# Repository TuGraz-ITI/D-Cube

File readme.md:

# D-Cube Benchmark #
The entire software stack for the ([public D-Cube instance](https://iti-testbed.tugraz.at/overview)) has been released as open-source as well and can be found ([here](https://github.com/TuGraz-ITI/D-Cube-Benchmark)). The initial documentation of the stack is avaialble ([here](https://tugraz-iti.github.io)).

# D-Cube Design #

D-Cube is published as open source hardware under [CC-BY-SA](license.md) ([online](https://creativecommons.org/licenses/by-sa/4.0/deed.en)).
D-Cube is a low-cost tool that allows to accurately profile the end-to-end delay, reliability, and power consumption, of low-power wireless sensor nodes, as well as to graphically visualize their evolution in real-time.
This tool has been used to set-up the EWSN 2016, 2017 and 2018 dependability competitions.
* [EWSN 2016 Dependability Competition (Graz, Austria)](http://ewsn2016.tugraz.at/cms/index.php?id=49)  
* [EWSN 2017 Dependability Competition (Uppsala, Sweden)](http://www.ewsn2017.org/dependability-competition1.html)
* [EWSN 2018 Dependability Competition (Madrid, Spain)](https://ewsn2018.networks.imdea.org/competition-program.html)
* [EWSN 2019 Dependability Competition (Beijing, China)](http://ewsn2019.thss.tsinghua.edu.cn/competition-scenario.html)

A scientific paper about D-Cube was published at the 14th International Conference on Embedded Wireless Systems and Networks (EWSN), and is available [here](http://www.carloalbertoboano.com/documents/boano17competition.pdf). 
An scientific paper describing D-Cube's binary patching capability and explaining how to use D-Cube to benchmark low-power wireless systems was published at the 1st International Workshop on Benchmarking Cyber-Physical Networks and Systems (CPSBench), and can be downloaded [here](http://www.carloalbertoboano.com/documents/schuss18benchmark.pdf).  
A set of slides giving a brief overview of D-Cube's capabilities and architecture can be found [here](http://www.carloalbertoboano.com/documents/D-Cube_overview.pdf).  

## D-Cube Hardware ##
The design files in this repository where used to fabricate the current iteration of D-Cube. The GPS module used is a Navspark-GL. For the complementary MOSFET a NTJD4105CT2G was chosen in the final design.

### The current version of the hardware (2.1) ###
The current version of the hardware supports multiple bi-directional GPIOs via isolation. It also adds support for PoE via a PEM1305 module. The aging navspark has been replaced with a more generic ublox neo footprint.

### The orignal version of the hardware (1.0) ###

### The prototype used during EWSN 2016 ###

## D-Cube Software ##
The Software consists of two parts
* A task reading the ADC into a FIFO (on top of a real-time Linux kernel)
* A task reading the FIFO and writing it to the database (InfluxDB)

D-Cube contains a power switch circuit which controls the power before the DCDC isolator. A high signal on GPIO23 is required for the ADC and the target to be supplied with power. The gpio.sh file contains an example for this.

### Real-Time Linux ###
We used https://github.com/emlid/linux-rt-rpi but others should work fine

### Visualisation ###
InfluxDB has many frontends available, we used grafana (http://grafana.org/)

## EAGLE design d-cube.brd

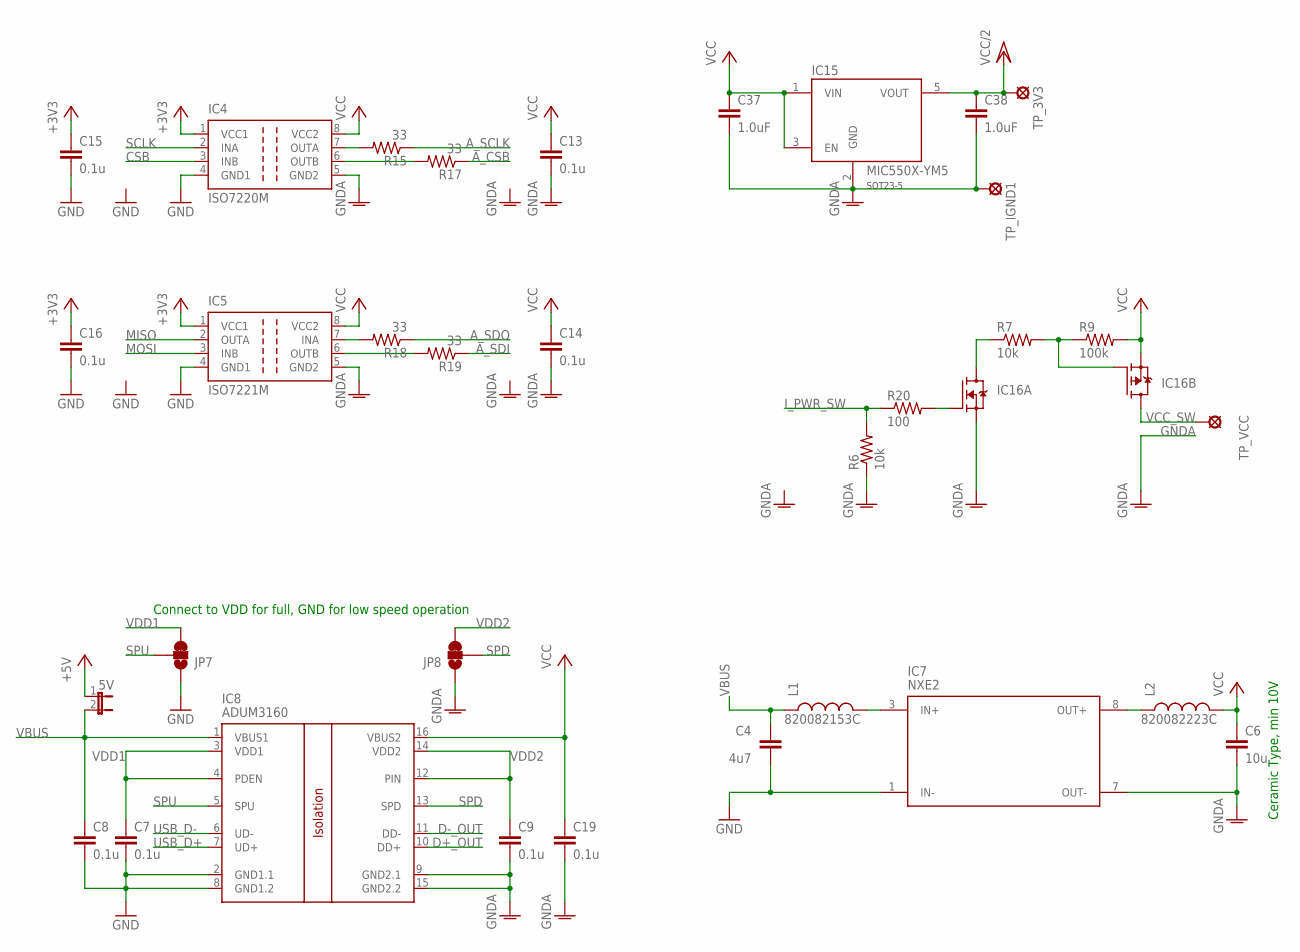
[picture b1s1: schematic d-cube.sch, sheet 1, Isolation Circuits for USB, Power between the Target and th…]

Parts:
5V: JP1E; JP1
C4: 4u7; 0805
C6: 10u; 0805
C7, C8, C9, C13, C14, C15, C16, C19: 0.1u; 0402-CAP
C37, C38: 1.0uF; 0805
IC4: ISO7220M; SO-08
IC5: ISO7221M; SO-08
IC7: NXE2
IC8: ADUM3160; SO-16W
IC15: MIC550X-YM5; SOT23-5-DBV
IC16: COMPLEMENTARY; SOT-363
JP7, JP8: JUMPER-PAD-3-2OF3_NC_BY_TRACE_LARGE; PAD-JUMPER-3-2OF3_NC_BY_TRACE_YES_SILK_LARGE
L1: 820082153C; 8200
L2: 820082223C; 8200
R6, R7: 10k; 0402-RES
R9: 100k; 0402-RES
R15, R17, R18, R19: 33; 0402-RES
R20: 100; 0402-RES
TP_3V3: LSP10
TP_IGND1: LSP10
TP_VCC: LSP10

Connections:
+3V3: C15.1, C16.1, IC4.1 (VCC1), IC5.1 (VCC1); also elsewhere on the board
+5V: 5V.1; also elsewhere on the board
A_CSB: R17.1; also elsewhere on the board
A_SCLK: R15.1; also elsewhere on the board
A_SDI: R19.1; also elsewhere on the board
A_SDO: R18.1; also elsewhere on the board
CSB: IC4.3 (INB); also elsewhere on the board
D+_OUT: IC8.10 (DD+); also elsewhere on the board
D-_OUT: IC8.11 (DD-); also elsewhere on the board
GND: C4.2, C7.2, C8.2, C15.2, C16.2, IC4.4 (GND1), IC5.4 (GND1), IC7.1 (IN-), IC8.2 (GND1.1), IC8.8 (GND1.2), JP7.1; also elsewhere on the board
GNDA: C6.2, C9.2, C13.2, C14.2, C19.2, C37.2, C38.2, IC4.5 (GND2), IC5.5 (GND2), IC7.7 (OUT-), IC8.9 (GND2.1), IC8.15 (GND2.2), IC15.2 (GND), IC16.1 (S), JP8.1, R6.1, TP_IGND1.MP; also elsewhere on the board
I_PWR_SW: R6.2, R20.1; also elsewhere on the board
MISO: IC5.2 (OUTA); also elsewhere on the board
MOSI: IC5.3 (INB); also elsewhere on the board
unnamed: IC7.3 (IN+), L1.P$2 (2)
unnamed: IC16.2 (G), R20.2
unnamed: IC16.5 (G), R7.2, R9.1
unnamed: IC7.8 (OUT+), L2.P$1 (1)
unnamed: IC16.6 (D), R7.1
unnamed: IC4.7 (OUTA), R15.2
unnamed: IC4.6 (OUTB), R17.2
unnamed: IC5.7 (INA), R18.2
unnamed: IC5.6 (OUTB), R19.2
SCLK: IC4.2 (INA); also elsewhere on the board
SPD: IC8.13 (SPD), JP8.2
SPU: IC8.5 (SPU), JP7.2
USB_D+: IC8.7 (UD+); also elsewhere on the board
USB_D-: IC8.6 (UD-); also elsewhere on the board
VBUS: 5V.2, C4.1, C8.1, IC8.1 (VBUS1), L1.P$1 (1); also elsewhere on the board
VCC: C6.1, C13.1, C14.1, C19.1, C37.1, IC4.8 (VCC2), IC5.8 (VCC2), IC8.16 (VBUS2), IC15.1 (VIN), IC15.3 (EN), IC16.4 (S), L2.P$2 (2), R9.2; also elsewhere on the board
VCC/2: C38.1, IC15.5 (VOUT), TP_3V3.MP; also elsewhere on the board
VCC_SW: IC16.3 (D), TP_VCC.MP; also elsewhere on the board
VDD1: C7.1, IC8.3 (VDD1), IC8.4 (PDEN), JP7.3
VDD2: C9.1, IC8.12 (PIN), IC8.14 (VDD2), JP8.3

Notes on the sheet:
Connect to VDD for full, GND for low speed operation
Ceramic Type, min 10V

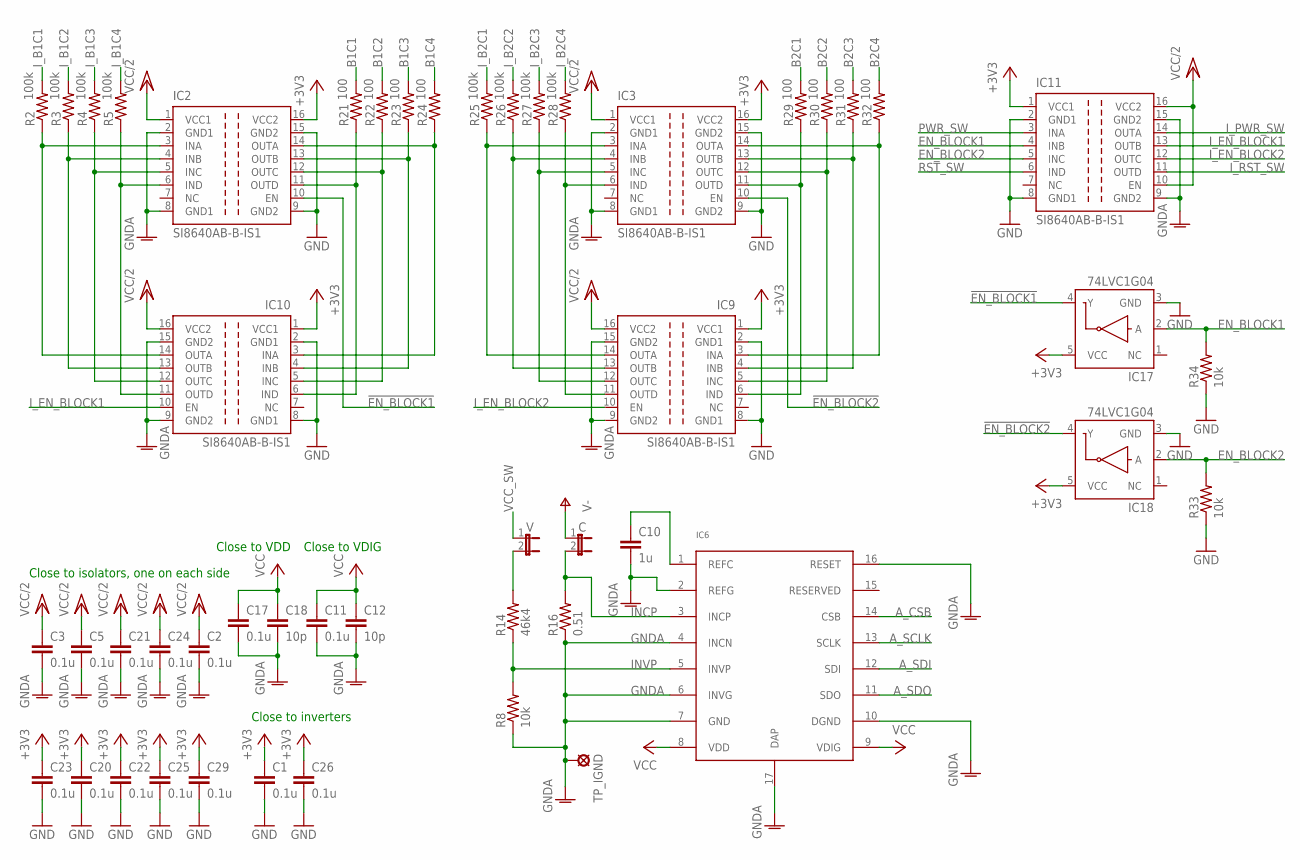
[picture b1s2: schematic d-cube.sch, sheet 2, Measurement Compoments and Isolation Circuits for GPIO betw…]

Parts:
C: JP1E; JP1
C1, C2, C3, C5, C11, C17, C20, C21, C22, C23, C24, C25, C26, C29: 0.1u; 0402-CAP
C10: 1u; 0402-CAP
C12, C18: 10p; 0402-CAP
IC2, IC3, IC9, IC10, IC11: SI8640AB-B-IS1; SO-16
IC6: LMP92064; WSON-16
IC17, IC18: 74LVC1G04; SOT353
R2, R3, R4, R5, R25, R26, R27, R28: 100k; 0402-RES
R8: 10k; 0805
R14: 46k4; 0805
R16: 0.51; 1206
R21, R22, R23, R24, R29, R30, R31, R32: 100; 0402-RES
R33, R34: 10k; 0402-RES
TP_IGND: LSP10
V: JP1E; JP1

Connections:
!EN_BLOCK1: IC2.10 (EN), IC17.4 (Y)
!EN_BLOCK2: IC3.10 (EN), IC18.4 (Y)
+3V3: C1.1, C20.1, C22.1, C23.1, C25.1, C26.1, C29.1, IC2.16 (VCC2), IC3.16 (VCC2), IC9.1 (VCC1), IC10.1 (VCC1), IC11.1 (VCC1), IC17.5 (VCC), IC18.5 (VCC); also elsewhere on the board
A_CSB: IC6.14 (CSB); also elsewhere on the board
A_SCLK: IC6.13 (SCLK); also elsewhere on the board
A_SDI: IC6.12 (SDI); also elsewhere on the board
A_SDO: IC6.11 (SDO); also elsewhere on the board
B1C1: R21.2; also elsewhere on the board
B1C2: R22.2; also elsewhere on the board
B1C3: R23.2; also elsewhere on the board
B1C4: R24.2; also elsewhere on the board
B2C1: R29.2; also elsewhere on the board
B2C2: R30.2; also elsewhere on the board
B2C3: R31.2; also elsewhere on the board
B2C4: R32.2; also elsewhere on the board
EN_BLOCK1: IC11.4 (INB), IC17.2 (A), R34.2; also elsewhere on the board
EN_BLOCK2: IC11.5 (INC), IC18.2 (A), R33.2; also elsewhere on the board
GND: C1.2, C20.2, C22.2, C23.2, C25.2, C26.2, C29.2, IC2.9 (GND2), IC2.15 (GND2), IC3.9 (GND2), IC3.15 (GND2), IC9.2 (GND1), IC9.8 (GND1), IC10.2 (GND1), IC10.8 (GND1), IC11.2 (GND1), IC11.8 (GND1), IC17.3 (GND), IC18.3 (GND), R33.1, R34.1; also elsewhere on the board
GNDA: C2.2, C3.2, C5.2, C10.2, C11.2, C12.2, C17.2, C18.2, C21.2, C24.2, IC2.2 (GND1), IC2.8 (GND1), IC3.2 (GND1), IC3.8 (GND1), IC6.2 (REFG), IC6.4 (INCN), IC6.6 (INVG), IC6.7 (GND), IC6.10 (DGND), IC6.16 (RESET), IC6.17 (DAP), IC9.9 (GND2), IC9.15 (GND2), IC10.9 (GND2), IC10.15 (GND2), IC11.9 (GND2), IC11.15 (GND2), R8.1, R16.1, TP_IGND.MP; also elsewhere on the board
INCP: C.2, IC6.3 (INCP), R16.2
INVP: IC6.5 (INVP), R8.2, R14.1
I_B1C1: R2.2; also elsewhere on the board
I_B1C2: R3.2; also elsewhere on the board
I_B1C3: R4.2; also elsewhere on the board
I_B1C4: R5.2; also elsewhere on the board
I_B2C1: R25.2; also elsewhere on the board
I_B2C2: R26.2; also elsewhere on the board
I_B2C3: R27.2; also elsewhere on the board
I_B2C4: R28.2; also elsewhere on the board
I_EN_BLOCK1: IC10.10 (EN), IC11.13 (OUTB)
I_EN_BLOCK2: IC9.10 (EN), IC11.12 (OUTC)
I_PWR_SW: IC11.14 (OUTA); also elsewhere on the board
I_RST_SW: IC11.11 (OUTD); also elsewhere on the board
unnamed: IC2.3 (INA), IC10.14 (OUTA), R2.1
unnamed: IC2.14 (OUTA), IC10.3 (INA), R24.1
unnamed: IC2.13 (OUTB), IC10.4 (INB), R23.1
unnamed: IC2.12 (OUTC), IC10.5 (INC), R22.1
unnamed: IC3.3 (INA), IC9.14 (OUTA), R25.1
unnamed: IC2.6 (IND), IC10.11 (OUTD), R5.1
unnamed: IC2.5 (INC), IC10.12 (OUTC), R4.1
unnamed: IC2.4 (INB), IC10.13 (OUTB), R3.1
unnamed: C10.1, IC6.1 (REFC)
unnamed: IC2.11 (OUTD), IC10.6 (IND), R21.1
unnamed: R14.2, V.2
unnamed: IC3.6 (IND), IC9.11 (OUTD), R28.1
unnamed: IC3.5 (INC), IC9.12 (OUTC), R27.1
unnamed: IC3.4 (INB), IC9.13 (OUTB), R26.1
unnamed: IC3.14 (OUTA), IC9.3 (INA), R32.1
unnamed: IC3.13 (OUTB), IC9.4 (INB), R31.1
unnamed: IC3.12 (OUTC), IC9.5 (INC), R30.1
unnamed: IC3.11 (OUTD), IC9.6 (IND), R29.1
PWR_SW: IC11.3 (INA); also elsewhere on the board
RST_SW: IC11.6 (IND); also elsewhere on the board
V-: C.1; also elsewhere on the board
VCC: C11.1, C12.1, C17.1, C18.1, IC6.8 (VDD), IC6.9 (VDIG); also elsewhere on the board
VCC/2: C2.1, C3.1, C5.1, C21.1, C24.1, IC2.1 (VCC1), IC3.1 (VCC1), IC9.16 (VCC2), IC10.16 (VCC2), IC11.10 (EN), IC11.16 (VCC2); also elsewhere on the board
VCC_SW: V.1; also elsewhere on the board

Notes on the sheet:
Close to inverters
Close to isolators, one on each side
Close to VDD
Close to VDIG

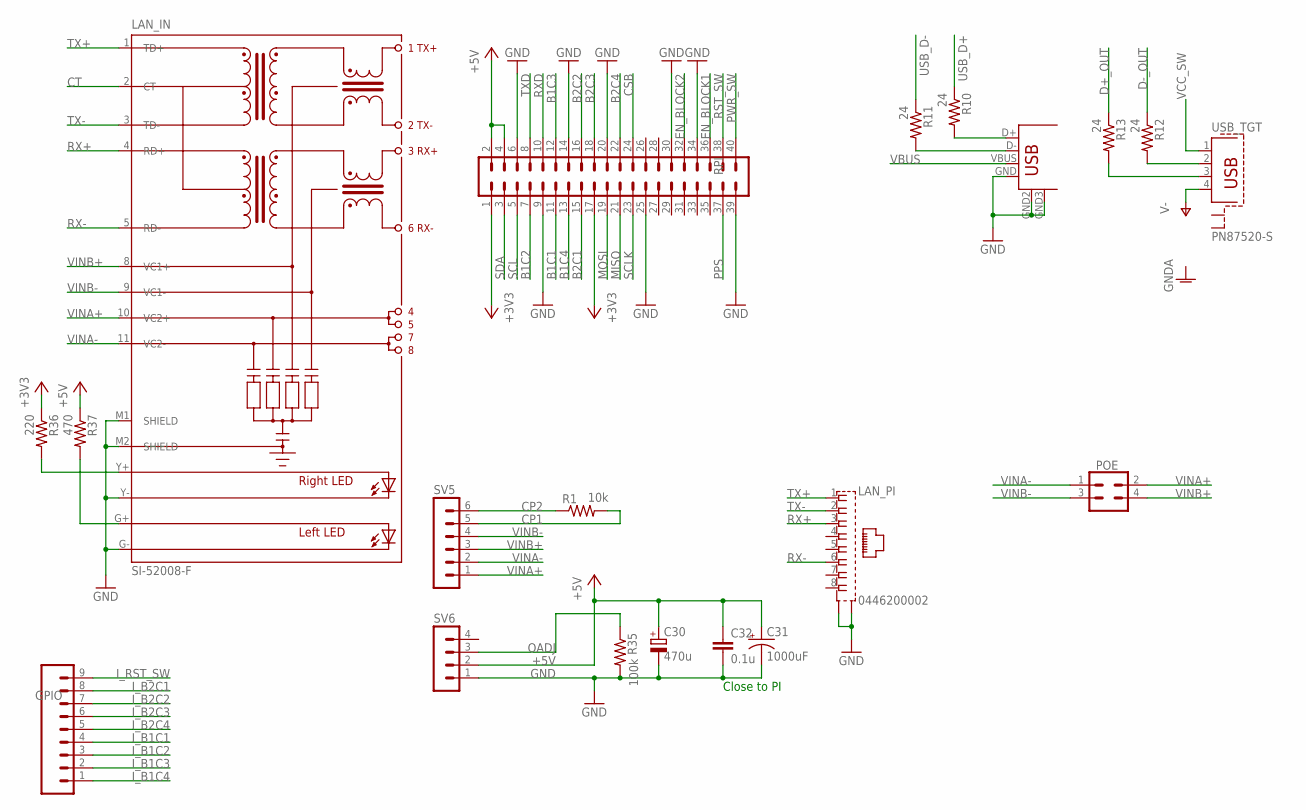
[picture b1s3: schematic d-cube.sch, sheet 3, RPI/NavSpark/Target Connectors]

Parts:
C30: 470u; CT7343
C31: 1000uF; PANASONIC_G
C32: 0.1u; 0805
GPIO: CONN_09NO_SILK; 1X09_NO_SILK
LAN_IN: SI-52008-F; POE
LAN_PI: 0446200002
POE: CONN_02X2; 2X02_NO_SILK
R1: 10k; 0402-RES
R10, R11, R12, R13: 24; 0402-RES
R35: 100k; 0402-RES
R36: 220; 0402-RES
R37: 470; 0402-RES
RPI: MA20-2
SV5: MA06-1
SV6: MA04-1
USB_PI: USB+SHIELDUSB-A-H-S; USB-A-H
USB_TGT: PN87520-S

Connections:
+3V3: R36.1, RPI.1, RPI.17; also elsewhere on the board
+5V: C30.+, C31.+, C32.1, R37.1, RPI.2, RPI.4, SV6.2; also elsewhere on the board
B1C1: RPI.11; also elsewhere on the board
B1C2: RPI.7; also elsewhere on the board
B1C3: RPI.12; also elsewhere on the board
B1C4: RPI.13; also elsewhere on the board
B2C1: RPI.15; also elsewhere on the board
B2C2: RPI.16; also elsewhere on the board
B2C3: RPI.18; also elsewhere on the board
B2C4: RPI.22; also elsewhere on the board
CP1: R1.2, SV5.5
CP2: R1.1, SV5.6
CSB: RPI.24; also elsewhere on the board
CT: LAN_IN.2 (CT)
D+_OUT: R13.1; also elsewhere on the board
D+_OUT_TERM: R13.2, USB_TGT.3
D-_OUT: R12.1; also elsewhere on the board
D-_OUT_TERM: R12.2, USB_TGT.2
EN_BLOCK1: RPI.36; also elsewhere on the board
EN_BLOCK2: RPI.32; also elsewhere on the board
GND: C30.-, C31.-, C32.2, LAN_IN.G- (C-L), LAN_IN.M1 (SHIELD), LAN_IN.M2 (SHIELD), LAN_IN.Y- (C-R), LAN_PI.S@1 (S1), LAN_PI.S@2 (S2), R35.2, RPI.6, RPI.9, RPI.14, RPI.20, RPI.25, RPI.30, RPI.34, RPI.39, SV6.1, USB_PI.GND, USB_PI.GND2 (S1), USB_PI.GND3 (S2); also elsewhere on the board
I_B1C1: GPIO.4; also elsewhere on the board
I_B1C2: GPIO.3; also elsewhere on the board
I_B1C3: GPIO.2; also elsewhere on the board
I_B1C4: GPIO.1; also elsewhere on the board
I_B2C1: GPIO.8; also elsewhere on the board
I_B2C2: GPIO.7; also elsewhere on the board
I_B2C3: GPIO.6; also elsewhere on the board
I_B2C4: GPIO.5; also elsewhere on the board
I_RST_SW: GPIO.9; also elsewhere on the board
MISO: RPI.21; also elsewhere on the board
MOSI: RPI.19; also elsewhere on the board
unnamed: LAN_IN.Y+ (A-R), R36.2
unnamed: LAN_IN.G+ (A-L), R37.2
OADJ: R35.1, SV6.3
PPS: RPI.37; also elsewhere on the board
PWR_SW: RPI.40; also elsewhere on the board
RST_SW: RPI.38; also elsewhere on the board
RX+: LAN_IN.4 (RD+), LAN_PI.3
RX-: LAN_IN.5 (RD-), LAN_PI.6
RXD: RPI.10; also elsewhere on the board
SCL: RPI.5; also elsewhere on the board
SCLK: RPI.23; also elsewhere on the board
SDA: RPI.3; also elsewhere on the board
TX+: LAN_IN.1 (TD+), LAN_PI.1
TX-: LAN_IN.3 (TD-), LAN_PI.2
TXD: RPI.8; also elsewhere on the board
USB_D+: R10.1; also elsewhere on the board
USB_D+_TERM: R10.2, USB_PI.D+
USB_D-: R11.1; also elsewhere on the board
USB_D-_TERM: R11.2, USB_PI.D-
V-: USB_TGT.4; also elsewhere on the board
VBUS: USB_PI.VBUS; also elsewhere on the board
VCC_SW: USB_TGT.1; also elsewhere on the board
VINA+: LAN_IN.10 (VC2+), POE.2, SV5.1
VINA-: LAN_IN.11 (VC2-), POE.1, SV5.2
VINB+: LAN_IN.8 (VC1+), POE.4, SV5.3
VINB-: LAN_IN.9 (VC1-), POE.3, SV5.4

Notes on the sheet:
Close to PI

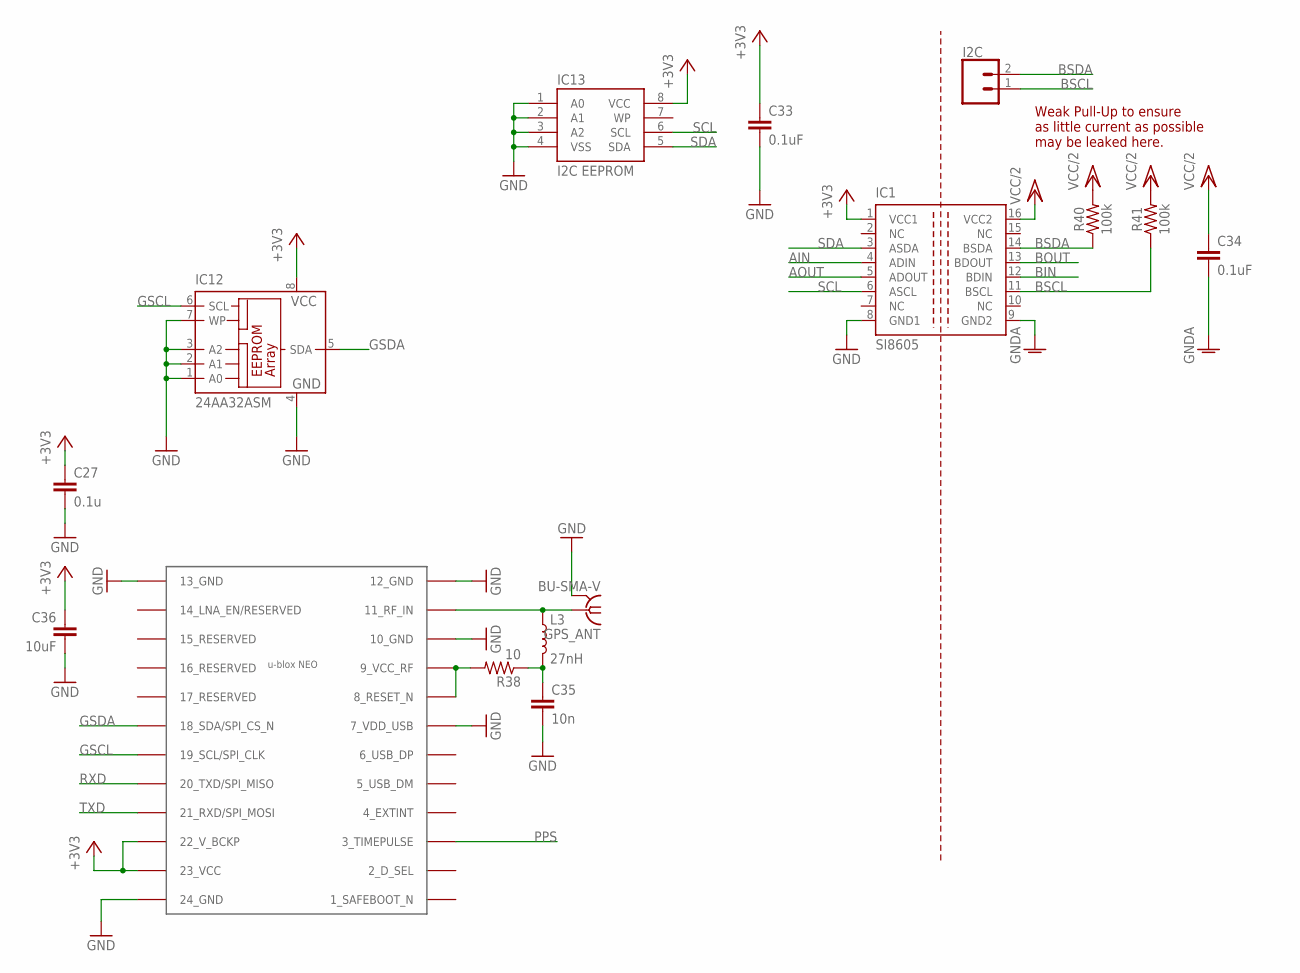
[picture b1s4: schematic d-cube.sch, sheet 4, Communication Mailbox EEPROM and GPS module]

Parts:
C27: 0.1u; 0402-CAP
C33, C34: 0.1uF; 0402
C35: 10n; 0805
C36: 10uF; 0805
GPS_ANT: BU-SMA-V
I2C: CONN_021X02_NO_SILK; 1X02_NO_SILK
IC1: SI8605; SO-16
IC12: 24AA32ASM; SO-08M
IC13: I2C EEPROM; SO08-EIAJ
IC14: NEO-M8
L3: 27nH; 0402
R38: 10; 0402-RES
R40, R41: 100k; 0402

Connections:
+3V3: C27.1, C33.1, C36.1, IC1.1 (VCC1), IC12.8 (VCC), IC13.8 (VCC), IC14.22 (22_V_BCKP), IC14.23 (23_VCC); also elsewhere on the board
AIN: IC1.4 (ADIN)
AOUT: IC1.5 (ADOUT)
BIN: IC1.12 (BDIN)
BOUT: IC1.13 (BDOUT)
BSCL: I2C.1, IC1.11 (BSCL), R41.1
BSDA: I2C.2, IC1.14 (BSDA), R40.1
GND: C27.2, C33.2, C35.2, C36.2, GPS_ANT.2 (GND), GPS_ANT.3 (GND), GPS_ANT.4 (GND), GPS_ANT.5 (GND), IC1.8 (GND1), IC12.1 (A0), IC12.2 (A1), IC12.3 (A2), IC12.4 (GND), IC12.7 (WP), IC13.1 (A0), IC13.2 (A1), IC13.3 (A2), IC13.4 (VSS), IC14.7 (7_VDD_USB), IC14.10 (10_GND), IC14.12 (12_GND), IC14.13 (13_GND), IC14.24 (24_GND); also elsewhere on the board
GNDA: C34.2, IC1.9 (GND2); also elsewhere on the board
GPS_SIG: GPS_ANT.1, IC14.11 (11_RF_IN), L3.1
GSCL: IC12.6 (SCL), IC14.19 (19_SCL/SPI_CLK)
GSDA: IC12.5 (SDA), IC14.18 (18_SDA/SPI_CS_N)
unnamed: IC14.8 (8_RESET_N), IC14.9 (9_VCC_RF), R38.2
unnamed: C35.1, L3.2, R38.1
PPS: IC14.3 (3_TIMEPULSE); also elsewhere on the board
RXD: IC14.20 (20_TXD/SPI_MISO); also elsewhere on the board
SCL: IC1.6 (ASCL), IC13.6 (SCL); also elsewhere on the board
SDA: IC1.3 (ASDA), IC13.5 (SDA); also elsewhere on the board
TXD: IC14.21 (21_RXD/SPI_MOSI); also elsewhere on the board
VCC/2: C34.1, IC1.16 (VCC2), R40.2, R41.2; also elsewhere on the board

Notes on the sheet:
Weak Pull-Up to ensure as little current as possible may be leaked here.

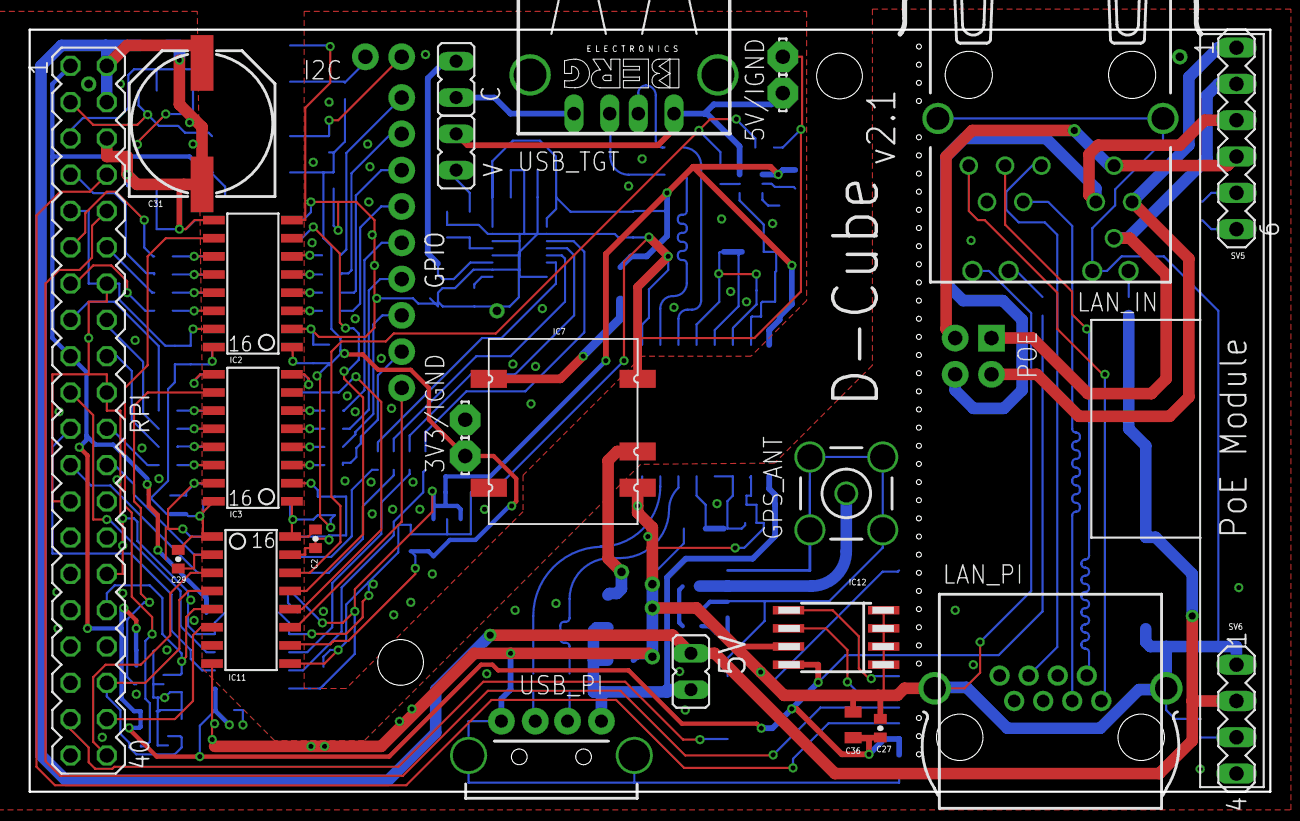
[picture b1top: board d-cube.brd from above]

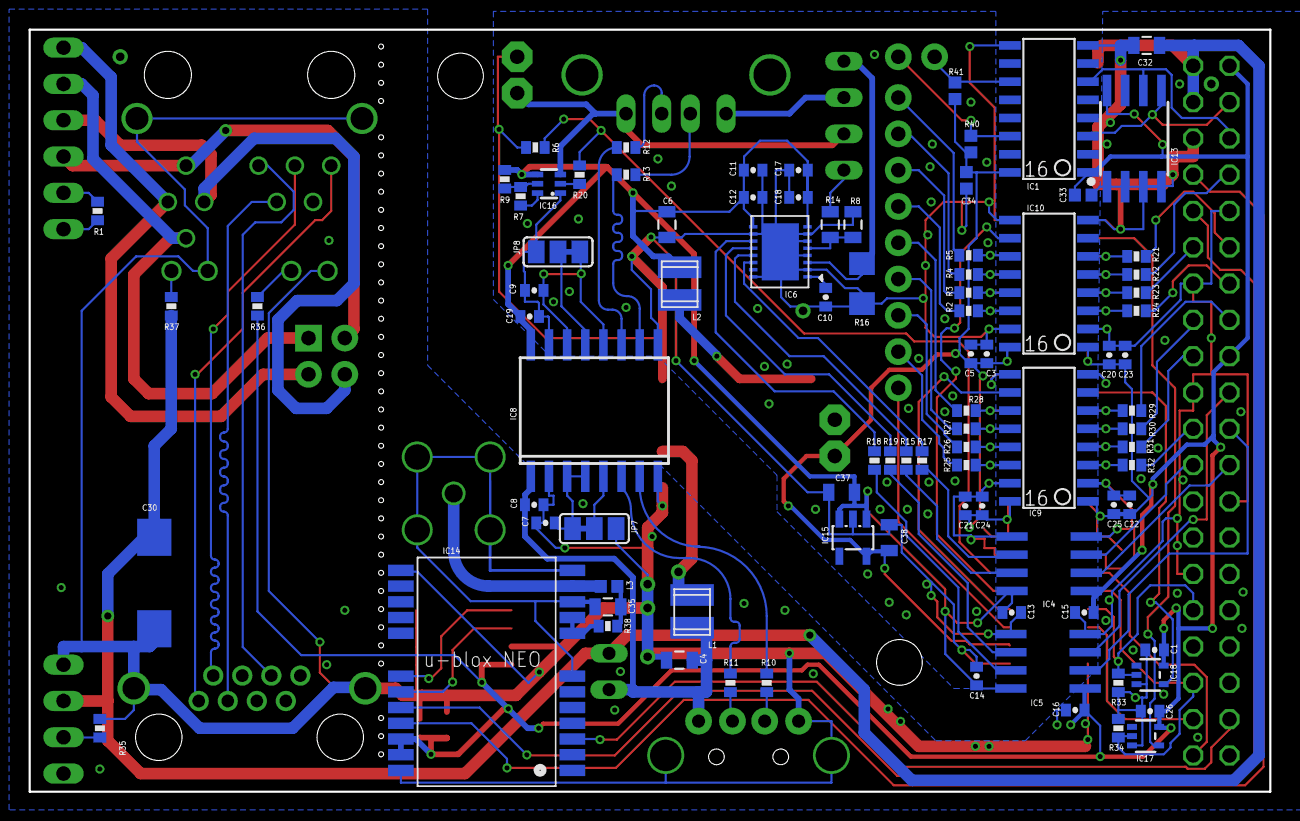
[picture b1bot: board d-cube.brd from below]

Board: 2 copper layers, 86.8 x 53.3 mm, 120 parts (91 on the bottom side), 109 nets.

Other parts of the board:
U$1, U$2: TU-LOGO-SMALL

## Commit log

2017-01-09 initial commit for public repo
2017-02-09 updated the readme for the ewsn2017 competition
2020-03-12 Added Photos of Version 2.1

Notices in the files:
parts and their libraries:
SparkFun-Passives: Licensing: Creative Commons ShareAlike 4.0 International - https://creativecommons.org/licenses/by-sa/4.0
